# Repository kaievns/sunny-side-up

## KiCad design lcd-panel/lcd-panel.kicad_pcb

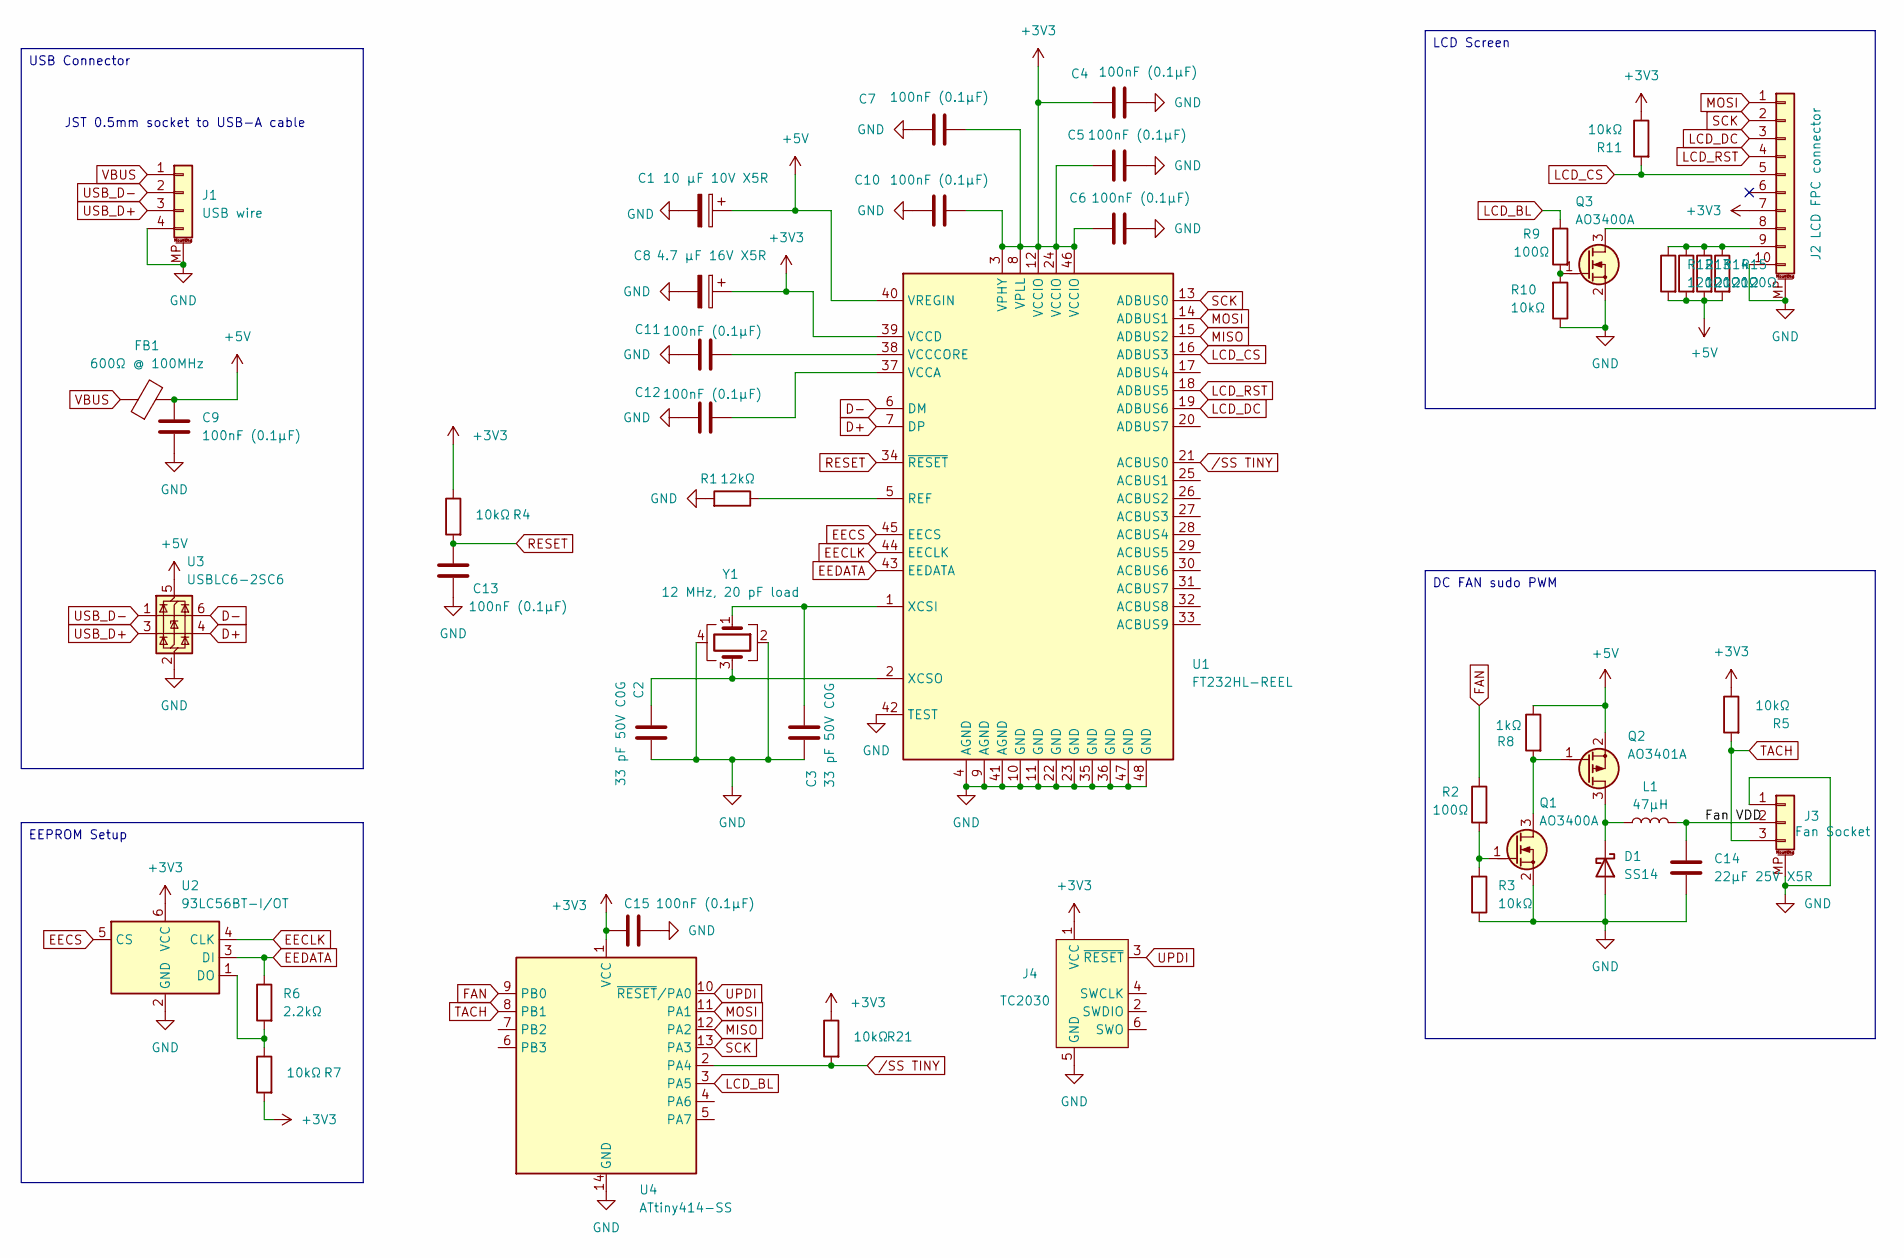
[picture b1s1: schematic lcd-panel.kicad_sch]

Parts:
C1: 10 µF 10V X5R; C_0603_1608Metric; LCSC C19702
C2, C3: 33 pF 50V C0G; C_0402_1005Metric; LCSC C1562
C4, C5, C6, C7, C9, C10, C11, C12, C13, C15: 100nF (0.1µF); C_0402_1005Metric; LCSC C1525
C8: 4.7 µF 16V X5R; C_0603_1608Metric; LCSC C19666
C14: 22µF 25V X5R; C_1206_3216Metric; LCSC C12891
D1: SS14; D_SMA; LCSC C2480
FB1: 600Ω @ 100MHz; L_0603_1608Metric; LCSC C96708
J1: USB wire; Molex_PicoBlade_53398-0471_1x04-1MP_P1.25mm_Vertical; LCSC C116890
J2: LCD FPC connector; Hirose_FH12-10S-0.5SH_1x10-1MP_P0.50mm_Horizontal; LCSC C5139870
J3: Fan Socket; Molex_PicoBlade_53398-0371_1x03-1MP_P1.25mm_Vertical; LCSC C88352
J4: TC2030; Tag-Connect_TC2030-IDC-NL_2x03_P1.27mm_Vertical
L1: 47µH; L_Sunlord_SWPA4018S; LCSC C83445
Q1, Q3: AO3400A; SOT-23; LCSC C20917
Q2: AO3401A; SOT-23; LCSC C15127
R1: 12kΩ; R_0402_1005Metric; LCSC C25752
R2, R9: 100Ω; R_0402_1005Metric; LCSC C25076
R3, R4, R5, R7, R10, R11, R21: 10kΩ; R_0402_1005Metric; LCSC C25744
R6: 2.2kΩ; R_0402_1005Metric; LCSC C25879
R8: 1kΩ; R_0402_1005Metric; LCSC C11702
R12, R13, R14, R15: 120Ω; R_0603_1608Metric; LCSC C22787
U1: FT232HL-REEL; LQFP-48_7x7mm_P0.5mm; LCSC C51997
U2: 93LC56BT-I/OT; SOT-23-6; LCSC C190271
U3: USBLC6-2SC6; SOT-23-6; LCSC C7519
U4: ATtiny414-SS; SOIC-14_3.9x8.7mm_P1.27mm
Y1: 12 MHz, 20 pF load; Crystal_SMD_3225-4Pin_3.2x2.5mm; LCSC C9002

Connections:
+3V3: C4.1, C5.1, C6.1, C7.2, C8.1, C10.2, C15.1, J2.7, J4.1 (VCC), R4.2, R5.2, R7.1, R11.2, R21.2, U1.3 (VPHY), U1.8 (VPLL), U1.12 (VCCIO), U1.24 (VCCIO), U1.39 (VCCD), U1.46 (VCCIO), U2.6 (VCC), U4.1 (VCC)
+5V: C1.1, C9.1, FB1.2, Q2.2 (S), R8.2, R12.1, R13.1, R14.1, R15.1, U1.40 (VREGIN), U3.5 (VBUS)
/Fan VDD: C14.1, J3.2, L1.2
D+: U1.7 (DP), U3.4 (I/O2)
D-: U1.6 (DM), U3.6 (I/O1)
EECLK: U1.44 (EECLK), U2.4 (CLK)
EECS: U1.45 (EECS), U2.5 (CS)
EEDATA: R6.2, U1.43 (EEDATA), U2.3 (DI)
FAN: R2.2, U4.9 (PB0)
GND: C1.2, C2.2, C3.2, C4.2, C5.2, C6.2, C7.1, C8.2, C9.2, C10.1, C11.1, C12.1, C13.1, C14.2, C15.2, D1.2 (A), J1.4, J1.MP (MountPin), J2.10, J2.MP (MountPin), J3.1, J3.MP (MountPin), J4.5 (GND), Q1.2 (S), Q3.2 (S), R1.1, R3.2, R10.2, U1.4 (AGND), U1.9 (AGND), U1.10 (GND), U1.11 (GND), U1.22 (GND), U1.23 (GND), U1.35 (GND), U1.36 (GND), U1.41 (AGND), U1.42 (TEST), U1.47 (GND), U1.48 (GND), U2.2 (GND), U3.2 (GND), U4.14 (GND), Y1.2, Y1.4
LCD_BL: R9.2, U4.3 (PA5)
LCD_CS: J2.5, R11.1, U1.16 (ADBUS3)
LCD_DC: J2.3, U1.19 (ADBUS6)
LCD_RST: J2.4, U1.18 (ADBUS5)
MISO: U1.15 (ADBUS2), U4.12 (PA2)
MOSI: J2.1, U1.14 (ADBUS1), U4.11 (PA1)
unnamed: D1.1 (K), L1.1, Q2.3 (D)
unnamed: J2.8, Q3.3 (D)
unnamed: J2.9, R12.2, R13.2, R14.2, R15.2
unnamed: Q1.3 (D), Q2.1 (G), R8.1
unnamed: Q1.1 (G), R2.1, R3.1
unnamed: Q3.1 (G), R9.1, R10.1
unnamed: R1.2, U1.5 (REF)
unnamed: C12.2, U1.37 (VCCA)
unnamed: C11.2, U1.38 (VCCCORE)
unnamed: C3.1, U1.1 (XCSI), Y1.1
unnamed: C2.1, U1.2 (XCSO), Y1.3
unnamed: R6.1, R7.2, U2.1 (DO)
RESET: C13.2, R4.1, U1.34 (~RESET)
SCK: J2.2, U1.13 (ADBUS0), U4.13 (PA3)
TACH: J3.3, R5.1, U4.8 (PB1)
UPDI: J4.3 (~RESET), U4.10 (~RESET/PA0)
USB_D+: J1.3, U3.3 (I/O2)
USB_D-: J1.2, U3.1 (I/O1)
VBUS: FB1.1, J1.1
/SS TINY: R21.1, U1.21 (ACBUS0), U4.2 (PA4)

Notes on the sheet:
JST 0.5mm socket to USB-A cable
LCD Screen
USB Connector
EEPROM Setup
DC FAN sudo PWM

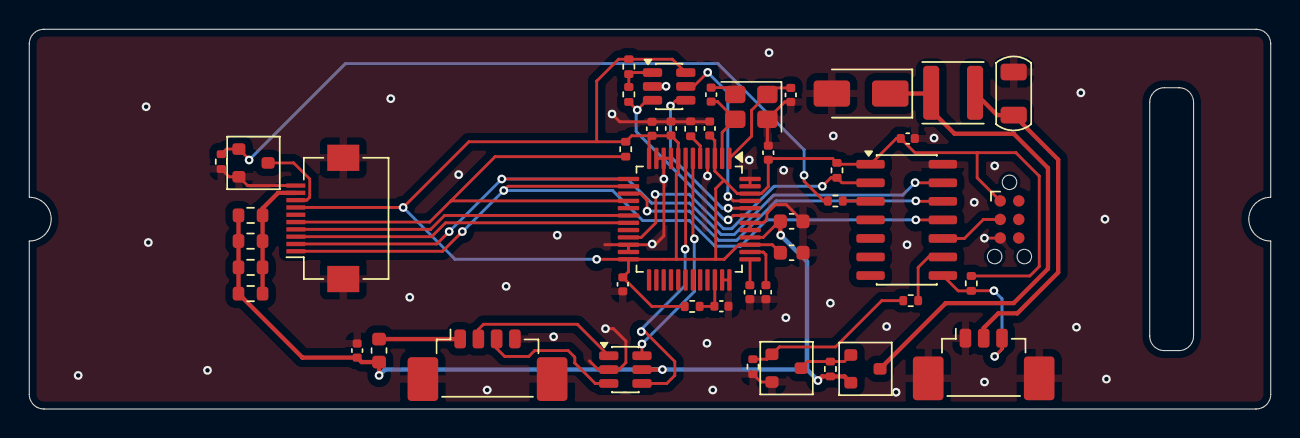
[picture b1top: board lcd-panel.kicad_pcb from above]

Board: 2 copper layers, 85.0 x 26.0 mm, 46 parts (0 on the bottom side), 36 nets.

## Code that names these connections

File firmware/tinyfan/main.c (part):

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 * tinyfan — ATtiny414 fan + backlight controller for the lcd-panel v2 board.
 *
 * Milestone 1 (per docs/v2-software-design.md): 10 MHz core, TCA0 split-mode
 * PWM (fan on PB0/WO0, backlight on PA5/WO5), an SPI slave speaking the 4-byte
 * CRC-8 framed protocol (PING / FAN_DUTY / BL / STATUS / FAILSAFE_CFG), tach
 * counting, a from-reset failsafe, and an inrush-safe soft-start on the fan.
 *
 * The ATtiny is a dumb executor: paneld owns the curve/policy. Firmware owns
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	}
}

/* tach: rising edges on PB1 */
ISR(PORTB_PORT_vect)
{
	if (PORTB.INTFLAGS & PIN1_bm) {
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
static void pwm_init(void)
{
	PORTB.DIRSET = PIN0_bm;   /* PB0 = fan (WO0) */
	PORTA.DIRSET = PIN5_bm;   /* PA5 = BL  (WO5) */

	TCA0.SPLIT.CTRLD = TCA_SPLIT_SPLITM_bm;
	TCA0.SPLIT.LPER  = FAN_PER;
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
static void spi_slave_init(void)
{
	/* Slave: MISO (PA2) is driven by the peripheral only while selected and
	 * tri-stated when /SS is high; MOSI/SCK/SS are inputs. R21 (external 10k)
	 * holds /SS high when the FT232H tri-states it. */
	PORTA.DIRSET = PIN2_bm;               /* MISO */
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
static void tach_init(void)
{
	/* PB1 input (default); R5 external 10k pull-up. Count rising edges. */
	PORTB.PIN1CTRL = PORT_ISC_RISING_gc;
}

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
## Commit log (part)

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2026-04-19 Throwing a basic kicad project with components
2026-04-20 Adding the fan control wiring
2026-04-20 Adding the baseline LCD wiring
2026-04-20 Brushing up BOM an sorting out power wiring
2026-04-20 Wiring the EEPROM
2026-04-21 Hooking up the crystal clock
2026-04-22 Filling up the rest of the schematic
2026-04-22 Loosely throwing compononents on the PCB
2026-04-22 Moving components to their proper positions
2026-04-22 Hooking up most of the wiring
2026-04-22 Mostly spit an polish
2026-04-24 Capturing the step file model
2026-04-24 Fine tuning the BOM for JLCPCBA components
2026-05-03 Swapping the LCD socket to the top connectors one
